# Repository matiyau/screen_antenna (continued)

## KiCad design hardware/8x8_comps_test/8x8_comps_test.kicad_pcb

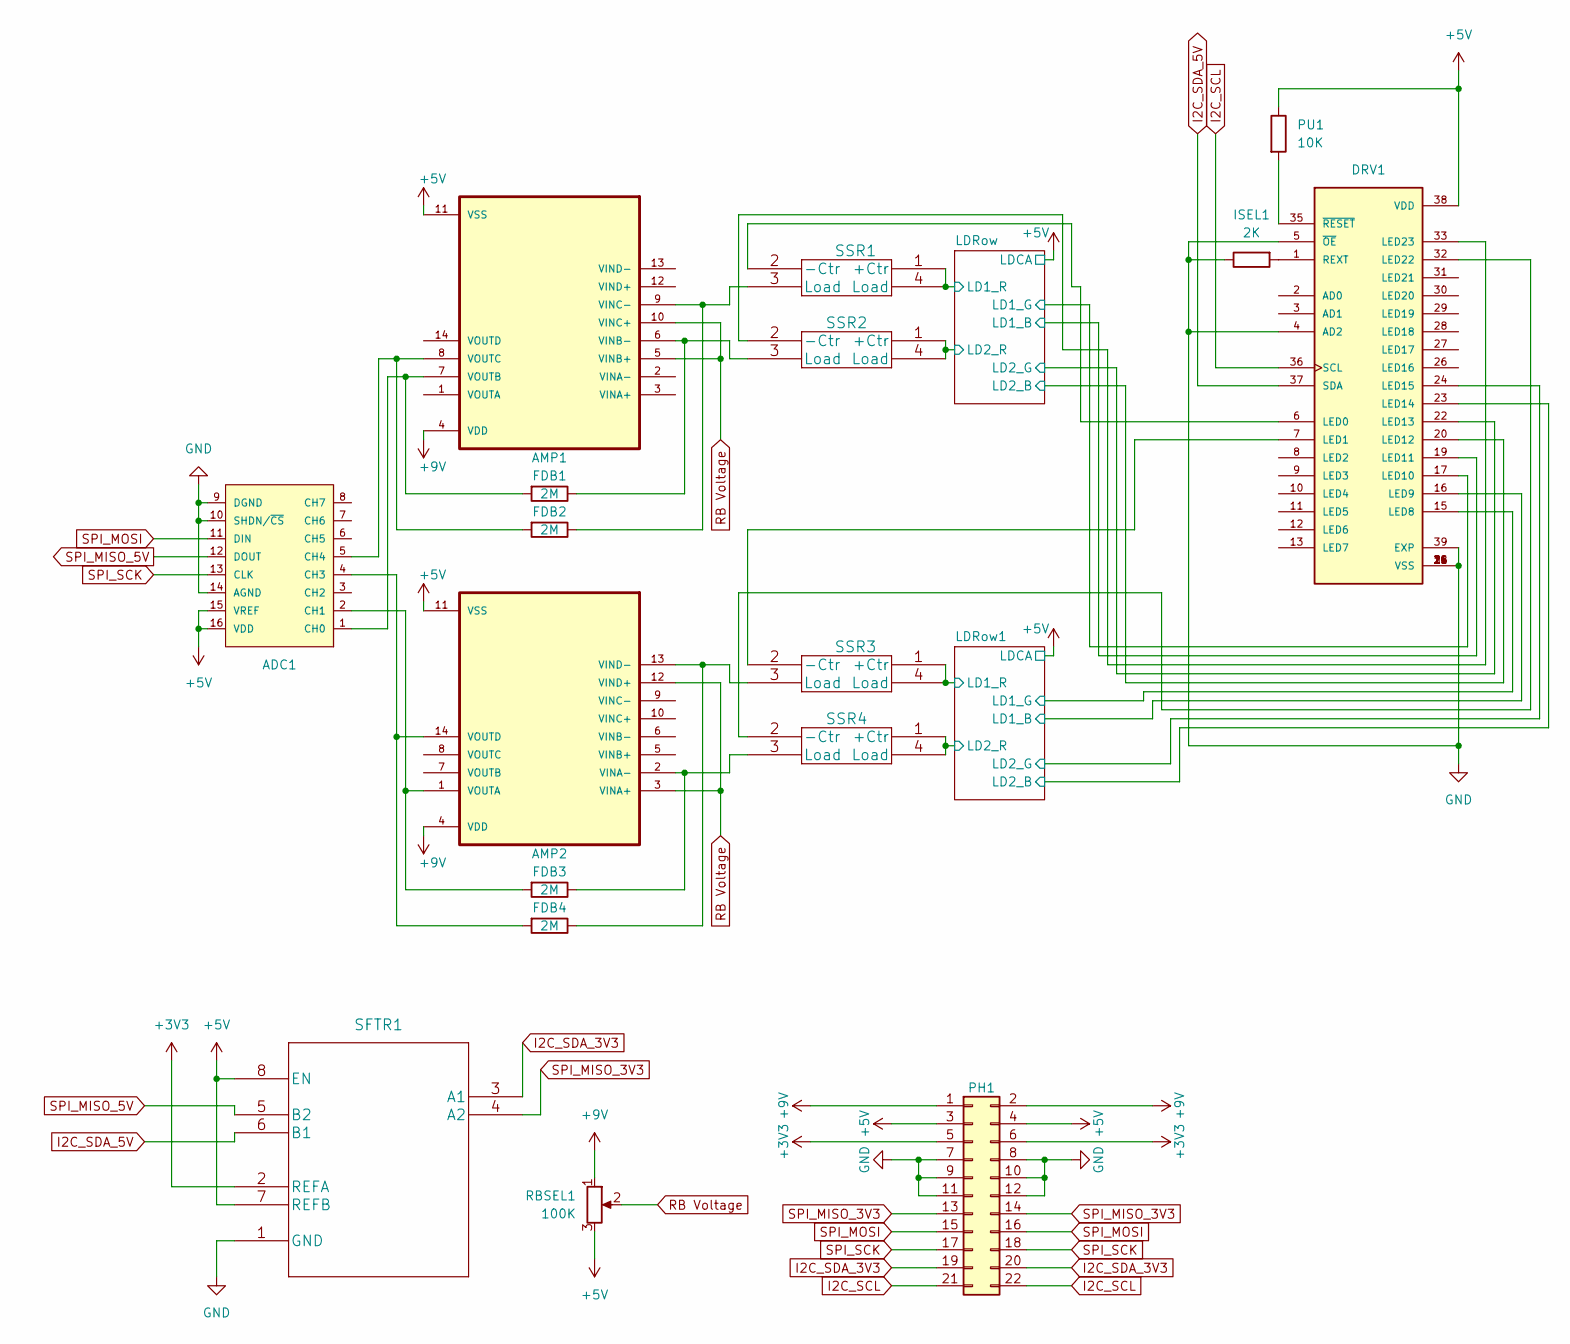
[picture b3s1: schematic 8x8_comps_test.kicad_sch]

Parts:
ADC1: MCU-MCP3008-I/P(DIP16-7.62MM); MCP3008-I&slash_P; MPN MCP3008-I/P
AMP1, AMP2: MCP619-I/SL; footprints
DRV1: PCA9956BTWY; SOP50P640X110-39N; PARTREV 1.1
FDB1, FDB2, FDB3, FDB4: 2M; footprints
ISEL1: 2K; footprints
PH1: Conn_02x11_Odd_Even; PinSocket_2x11_P2.54mm_Vertical
PU1: 10K; footprints
RBSEL1: 100K; Potentiometer_Runtron_RM-065_Vertical
SFTR1: LSF0102DCH
SSR1, SSR2, SSR3, SSR4: TLP417A-TP-F; footprints

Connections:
+3V3: PH1.5, PH1.6, SFTR1.2 (REFA)
+5V: ADC1.15 (VREF), ADC1.16 (VDD), AMP1.11 (VSS), AMP2.11 (VSS), DRV1.38 (VDD), PH1.3, PH1.4, PU1.1, RBSEL1.3, SFTR1.7 (REFB), SFTR1.8 (EN); also elsewhere on the board
+9V: AMP1.4 (VDD), AMP2.4 (VDD), PH1.1, PH1.2, RBSEL1.1
/LDRow1/LD1_B: DRV1.16 (LED9); also elsewhere on the board
/LDRow1/LD1_G: DRV1.15 (LED8); also elsewhere on the board
/LDRow1/LD1_R: SSR3.1 (+Ctr), SSR3.4 (Load); also elsewhere on the board
/LDRow1/LD2_B: DRV1.23 (LED14); also elsewhere on the board
/LDRow1/LD2_G: DRV1.24 (LED15); also elsewhere on the board
/LDRow1/LD2_R: SSR4.1 (+Ctr), SSR4.4 (Load); also elsewhere on the board
/LDRow/LD1_B: DRV1.19 (LED11); also elsewhere on the board
/LDRow/LD1_G: DRV1.17 (LED10); also elsewhere on the board
/LDRow/LD1_R: SSR1.1 (+Ctr), SSR1.4 (Load); also elsewhere on the board
/LDRow/LD2_B: DRV1.20 (LED12); also elsewhere on the board
/LDRow/LD2_G: DRV1.22 (LED13); also elsewhere on the board
/LDRow/LD2_R: SSR2.1 (+Ctr), SSR2.4 (Load); also elsewhere on the board
GND: ADC1.9 (DGND), ADC1.10 (SHDN/~CS), ADC1.14 (AGND), DRV1.4 (AD2), DRV1.5 (~OE), DRV1.14 (VSS), DRV1.18 (VSS), DRV1.21 (VSS), DRV1.25 (VSS), DRV1.34 (VSS), DRV1.39 (EXP), ISEL1.1, PH1.7, PH1.8, PH1.9, PH1.10, PH1.11, PH1.12, SFTR1.1 (GND)
I2C_SCL: DRV1.36 (SCL), PH1.21, PH1.22
I2C_SDA_3V3: PH1.19, PH1.20, SFTR1.3 (A1)
I2C_SDA_5V: DRV1.37 (SDA), SFTR1.6 (B1)
unnamed: ADC1.1 (CH0), AMP1.7 (VOUTB), FDB1.2
unnamed: ADC1.2 (CH1), AMP2.1 (VOUTA), FDB3.2
unnamed: ADC1.5 (CH4), AMP1.8 (VOUTC), FDB2.2
unnamed: AMP1.6 (VINB-), FDB1.1, SSR2.3 (Load)
unnamed: AMP1.9 (VINC-), FDB2.1, SSR1.3 (Load)
unnamed: AMP2.2 (VINA-), FDB3.1, SSR4.3 (Load)
unnamed: AMP2.13 (VIND-), FDB4.1, SSR3.3 (Load)
unnamed: ADC1.4 (CH3), AMP2.14 (VOUTD), FDB4.2
unnamed: DRV1.6 (LED0), SSR1.2 (-Ctr)
unnamed: DRV1.7 (LED1), SSR3.2 (-Ctr)
unnamed: DRV1.32 (LED22), SSR4.2 (-Ctr)
unnamed: DRV1.33 (LED23), SSR2.2 (-Ctr)
unnamed: DRV1.1 (REXT), ISEL1.2
unnamed: DRV1.35 (~RESET), PU1.2
RB Voltage: AMP1.5 (VINB+), AMP1.10 (VINC+), AMP2.3 (VINA+), AMP2.12 (VIND+), RBSEL1.2
SPI_MISO_3V3: PH1.13, PH1.14, SFTR1.4 (A2)
SPI_MISO_5V: ADC1.12 (DOUT), SFTR1.5 (B2)
SPI_MOSI: ADC1.11 (DIN), PH1.15, PH1.16
SPI_SCK: ADC1.13 (CLK), PH1.17, PH1.18

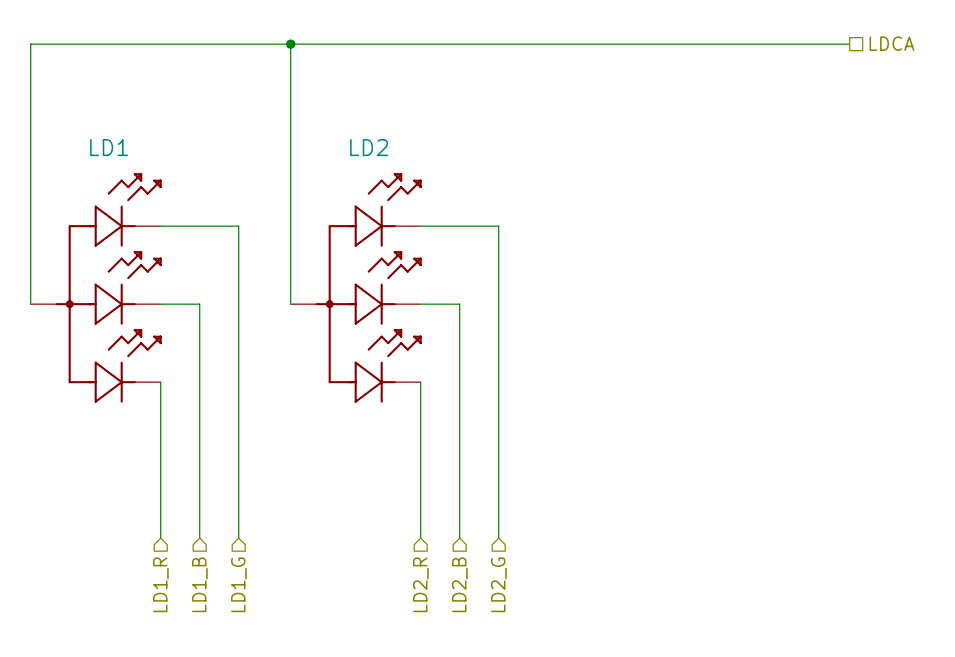
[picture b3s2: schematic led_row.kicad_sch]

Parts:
LD1, LD2: WP154A4SEJ3VBDZGC/CA; WP154A4SEJ3VBDZGC&slash_CA

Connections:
+5V: LD1.2 (CA), LD2.2 (CA); also elsewhere on the board
/LDRow/LD1_B: LD1.3 (B); also elsewhere on the board
/LDRow/LD1_G: LD1.4 (G); also elsewhere on the board
/LDRow/LD1_R: LD1.1 (R); also elsewhere on the board
/LDRow/LD2_B: LD2.3 (B); also elsewhere on the board
/LDRow/LD2_G: LD2.4 (G); also elsewhere on the board
/LDRow/LD2_R: LD2.1 (R); also elsewhere on the board

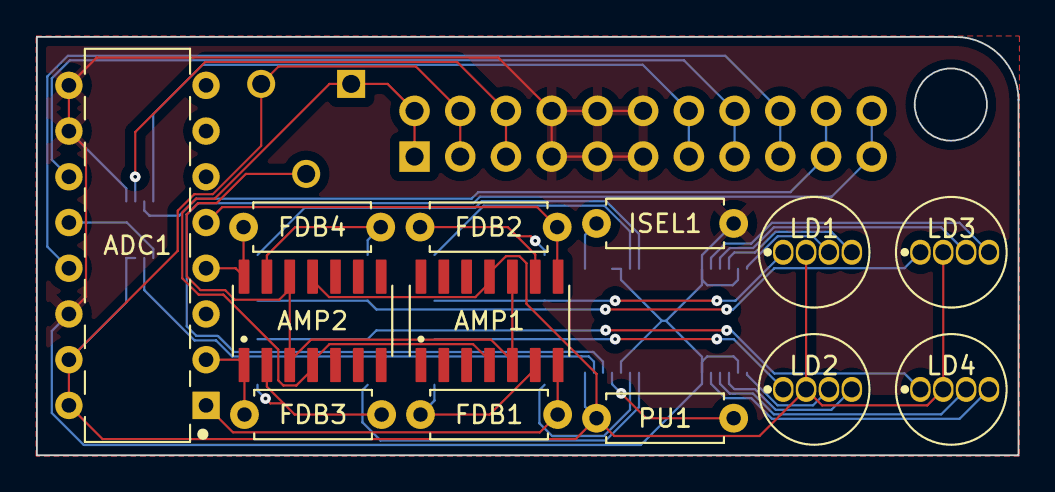
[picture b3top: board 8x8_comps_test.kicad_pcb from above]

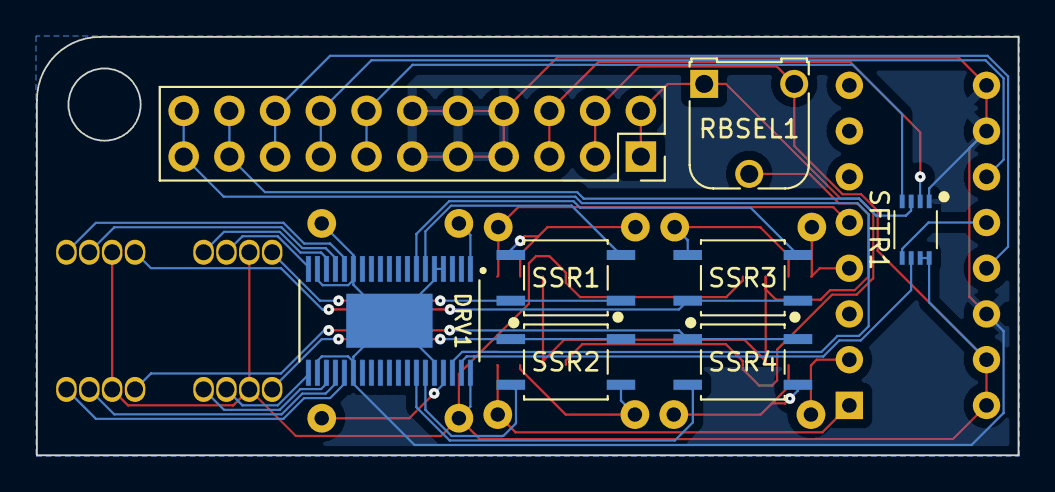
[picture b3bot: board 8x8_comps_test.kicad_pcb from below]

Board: 2 copper layers, 54.5 x 23.2 mm, 21 parts (8 on the bottom side), 38 nets.

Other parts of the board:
LD3, LD4: WP154A4SEJ3VBDZGC/CA; WP154A4SEJ3VBDZGC&slash_CA

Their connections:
+5V: LD3.2 (CA), LD4.2 (CA); also elsewhere on the board
/LDRow1/LD1_B: LD3.3 (B); also elsewhere on the board
/LDRow1/LD1_G: LD3.4 (G); also elsewhere on the board
/LDRow1/LD1_R: LD3.1 (R); also elsewhere on the board
/LDRow1/LD2_B: LD4.3 (B); also elsewhere on the board
/LDRow1/LD2_G: LD4.4 (G); also elsewhere on the board
/LDRow1/LD2_R: LD4.1 (R); also elsewhere on the board

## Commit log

2022-09-25 Added gitignore for Hardware
2022-09-25 Added Design Rules, Symbols and Schematics
2022-09-25 Created KiCAD Project with Symbols, Footprints, and Design Rules
2022-09-27 Updated KiCAD Libraries
2022-09-27 Added 8x8 Schematics
2022-09-27 Updated Pin Headers
2022-09-27 Updated LED Driver Footprints
2022-09-27 Modified LED Footprint
2022-09-27 Fixed Footprints
2022-09-27 Temporary Component Placement on PCB
2022-09-27 Rearranged PCB Components
2022-09-27 Boundary Change
2022-09-29 Added Project for Testing Components
2022-09-29 Fixed ADC Orientation
2022-09-30 Added test Schematic and PCB
2022-09-30 Changed Test Layout
2022-10-04 Updated Components
2022-10-05 Updated Footprints
2022-10-05 Updated Placement
2022-10-05 Designed PCB for Components Test
2022-10-07 Completed Major Routing
2022-10-07 Completed 8x8 Routing
2022-10-07 Updated 3D Models
2022-10-10 Updated PCB
2022-10-10 Added Dimensions to PCB
2022-11-04 Created 2x2 Software Project
2022-11-04 Updated One 4x2-Right Block
2022-11-04 Updated All Right Blocks & One 4x2 Left Block
2022-11-04 Completed Block Routing. Communication Left
2022-11-04 Updated Trace Widths and Ground Fill
2022-11-12 Updated Trace
2023-01-26 Reorganized File Structure
2023-01-26 Added Port Detection
2023-06-05 Added Screen Antenna Skeleton
2023-06-05 Added HW Files
2023-06-05 Added Timer Lib for Due
2023-06-05 Added Just Noticeable Colour Difference Scripts
2023-06-05 Added Mod Timer
2023-06-08 Added Support for Different Sketches
2023-06-15 Rx-Tx Performance Improvement
2023-07-03 Added additional files from the project timeline
2023-07-03 Delta-E For R_max Approximations Added
2023-07-03 Fixed .gitignore
2023-07-04 Fixed Plot Ticks
